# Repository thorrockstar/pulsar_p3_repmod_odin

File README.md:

Open Source Pulsar P3 Replacement Module 'Odin' & 'Loki'
========================================================

This project bundles my source code, binary, schematics and PCB layout files for my own Open Source Pulsar P3 LED watch replacement modules. I do **not** sell those modules or any component and I do **not** do any repairs. This project is purely for the enthusiast, that want to fix a Pulsar LED watch himself or herself, that is far beyond repair otherwise. This project is **not** meant to be used commercially.

The PCB layout is made in a way, allowing it to be opened and edited with the free Eagle version. I prefer the older Eagle 6.6 release, that still was made by CADSoft.

The free trial version of the CAD-Soft Eagle software can be found on CAD-Softs's own FTP server:
http://eagle.autodesk.com/eagle/software-versions/10

P3 Module Types
===============

This project contains two different boards. The **Odin Mark II** board, that can be used, if the **original Litronix** dotty LED display could be rescued. The **Loki** board can be used if the original display is broken and shall be replaced with four USSR made **AL304G replacement** single digit displays with common anodes. See the comments in the schematics.

**Note:** Some of the photos show **older** variants of the boards. So don't get confused. The current Odin Mark II features **4 extra transistors** for driving the common cathodes.

**Important Note:** As the new PCB's have traces and vias/pads on the back side, make sure you put some black isolation tape on top of the plastic carrier *before* placing the new PCB onto it. Otherwise the battery connection wires may short your PCB!

P4 Module Variant
=================

There is a sub-folder called 'p4mod', that contains a module called **Sif**. This one can be used for P4 Executive watches. It has the micro controller on the back side. So, double check the orientation of the chip, when soldering, as the PCB is shown from the top layer in the pictures and you need to turn the PCB over when soldering. Be aware, that you will need to **modify the plastic carrier**. You will be in need to make the open space behind the PCB wider, to be able to place the PCB flush on the P4 plastic carrier. I usually do that by cutting the edges on the top and bottom of the inner opening in order to create a 45 degree angle there.

License Agreement
=================

The software, source code, schematics, drawings and resources are provided to you by the Licensor under the License, as defined below, subject to the following condition.

Without limiting other conditions in the License, the grant of rights under the License will not include, and the License does not grant to you, the right to sell the software, source code, schematics, drawings or resources.

The Licensor does not grant the right to produce watch modules on the base of this work and then sell them as a product for profit.

These schematics, layout and source code files are free software; you can redistribute them and/or modify them under the terms of the GNU General Public License as published by the Free Software Foundation in version 2 of the License.

These source code, schematics, drawings and layout files are distributed in the hope that they will be useful, but WITHOUT ANY WARRANTY; without even the implied warranty of MERCHANTABILITY or FITNESS FOR A PARTICULAR PURPOSE. See the GNU General Public License for more details.

Hardware & Software
===================

This project features a MicroChip PIC18F24J11 MCU. The software can be compiled using Microchip's MPLAB IDE and the XC8 compiler. You can get those free for private use. To flash the controller I used a PICKIT™3 unit. You still get those units second hand or NOS but you can also use a more recent one.

**Module 'Odin' featuring the original display and light sensor.**

(Older Odin 1)

(Newer Odin Mark II)

In the main header file, select the right type of watch module. You find also ready compiled binaries for the 'Odin' and 'Loki' module.

**Module 'Loki' featuring four replacement single digit displays and no light sensor.**

Important
==========
We do **not** do any repairs or deliver any components. This is a pure Open Source project, were I share my files, that I used to create a replacement module for one of my old watches, that was corroded beyond repair. This project shall not be used commercially.

Contributing
============
To contribute to this project you should submit your proposals to the maintainer via GitHub.

Maintainer
==========
Dipl.-Ing.(FH) Roy Schneider

Useful Information
==================

More information about old Pulsar LED watches, can be found here:

Pulsar LED Watch Forum:
http://www.oldpulsars.com/

PCB
===

If you order your PCB at some manufacturer, go for the 1mm material thickness, not more. You need a thin PCB to ensure, you have enough clearance to the watch case glass, when the display has been installed. A traces thickness of 35 µm is good enough. Order the PCB with a solder stop mask. That simplifies soldering a lot. You usually do not need a silk screen. Order ENIG (Electroless Nickel Gold) surface (traces) for best solder results.

Energy Consumption
==================

The watch currently draws about 7 µA (0.007 mA) of current, if the display is not lit up. Assuming your silver oxide batteries would have 160mAh, the battery life time would be a year, depending how often you use the display. You may use Alkaline batteries but I suggest to use Silver Oxide batteries having 1.55V and a larger capacity.

Setting the Time & Date of the Replacement Module
=================================================

To forward the hours, place the magnet in the HOURS recess. To forward the minutes, place the magnet in the MINUTES recess. Keep in mind that the watch will stop counting the time, if you have forwarded the minutes, until you will press the first time the readout TIME button. This gives you an easy way to set the watch second-accurate, by setting the watch one minute into the future and then wait until the reference clock wraps to that very minute. If you press the TIME button in that moment, the watch will continue counting the time, having set the seconds to zero. To forward the month hold the DATE button pressed and place the magnet in the HOUR recess. To forward the day hold the DATE and TIME buttons pressed at the same time and place the magnet in the HOUR recess. This replacement module adds the weekday, the year and the light sensor read-out to the watch. Refer to the next chapter for setting them.

Settings the Extra Features of the Firmware not included in the original P3
===========================================================================

The firmware for this replacement module adds two additional functions to the watch. It adds the weekday and the year. To set the year hold the DATE and TIME button pressed and forward the year by putting the magnet into the MIN recess. To set the weekday hold only the DATE button pressed and forward the weekday by putting the magnet into the MIN recess. If you face the issue that you set the year instead of the weekday, then the magnet is very strong and engages not only the MIN but also the TIME reed contact. Try turning the magnet around in that case.

Optional Alarm Feature of the 'Loki Module'
============================================

This feature is only available for the 'Loki' modules, using the USSR made replacement displays. You can use the output RC2 of the micro controller in order to drive a disc piezo buzzer with a 820Ohm...1kOhm resistor in series. To use that feature turn the ALARM option on in the main.h header file and rebuild the binary.

**Note:**

Don't expect the alarm to be loud... it will not be loud enough to wake you up, simply because it is silenced by the massive metal case of the watch. :-)

**Set Alarm**

In order to set the alarm, press the TIME (hold) and then the DATE (hold) button in this exact order ands keep them pressed together. Now you can place the magnet in the HOUR or MIN recess to set the alarm.

**Toggle Alarm (on/off)**

To turn the alarm on or off press the TIME (hold) and then the DATE (hold) button in this exact order, then release the DATE button and press DATE again, while holding TIME still pressed, in order to toggle the alarm. A little dot on the right of the last AL304G display will indicate if the alarm is on or off.

Light Sensor Readout
====================

This applies only to the 'Odin' modules, if the light sensor option has been turned on. If you hold the DATE button pressed for more than a second, the watch will show the weekday and then, if you still keep the button pressed, the year. If you keep the button even longer pressed, a number will appear, that reflects the light sensor value. On normal daylight, that value shall be between two and four. On strong sun light five to six. If you are in dim light, the watch shall show one or zero. This readout is meant to make it easy to check, if the light sensor is working correctly.

Calibration
===========

The real-time crystal signal can be calibrated, so that the watch can provide an error of less than three seconds per month. If using the vintage original crystal, you will have easily 5 to 20 seconds drift per week, as those crystals are often hopelessly out tuned. By pressing the DATE button and holding it pressed, until the year or light sensor read out appears and then pressing the TIME button as well for a second, you will enter the drift calibration mode. You can now release the TIME button but keep the DATE pressed and use the magnet in the MIN recess to increase the calibration value. Use the HOUR recess to decrease the calibration value again. A positive value will speed up the watch by x\*0.6 seconds per week. A negative value will slow down the watch by x\*0.6 seconds by week. You can adjust the watch by a maximum ±38.76 seconds per week.

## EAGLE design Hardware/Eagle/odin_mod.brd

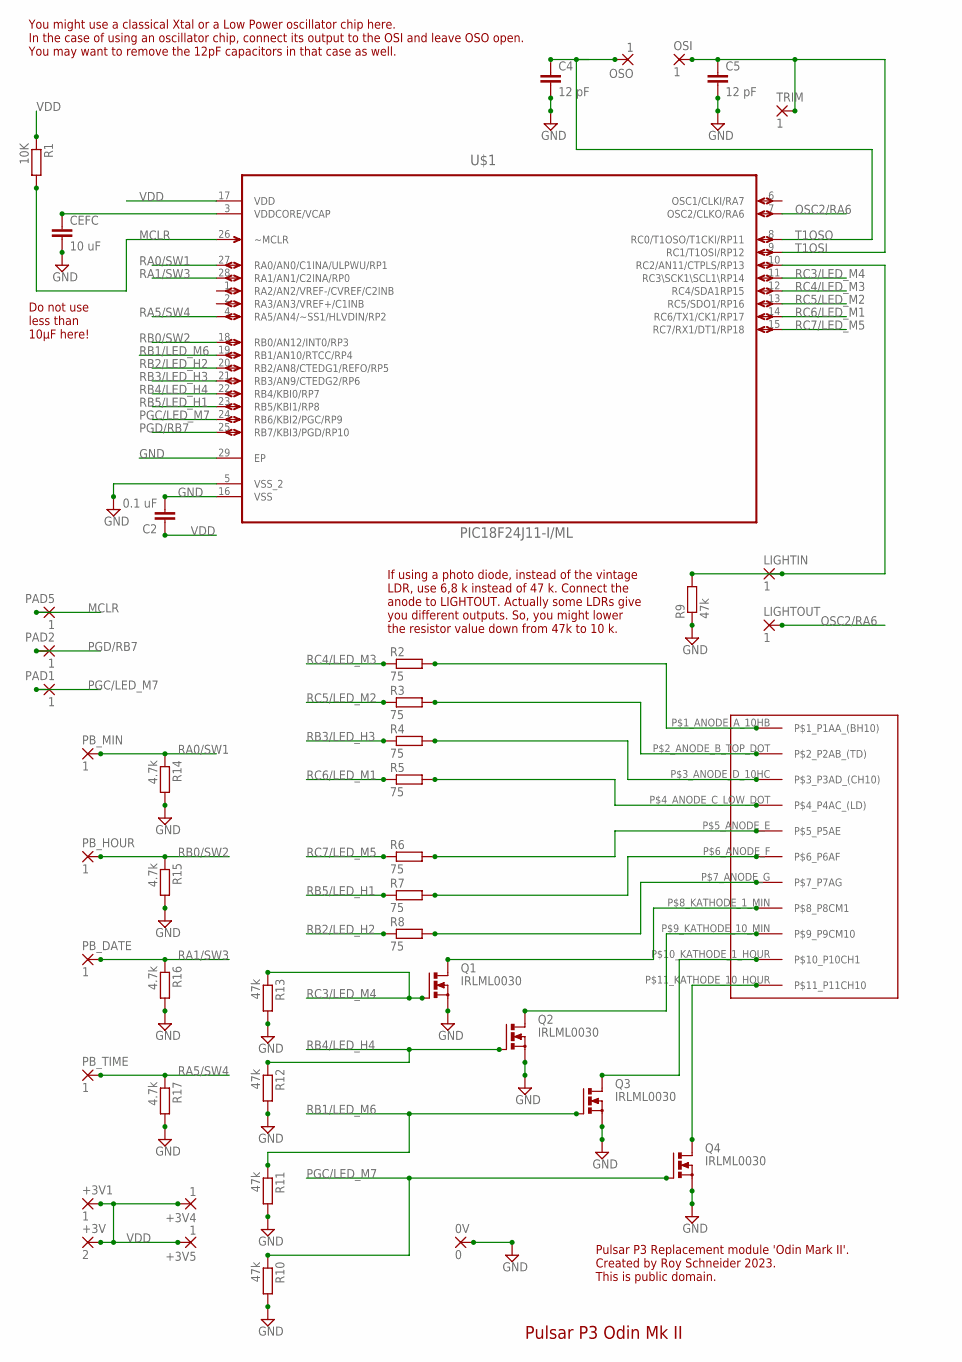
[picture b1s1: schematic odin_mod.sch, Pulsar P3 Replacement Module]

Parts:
0V: 0; SMD1,27-2,54
+3V: 2; SMD1,27-2,54
+3V1, +3V4, +3V5: 1; SMD1,27-2,54
C2: 0.1 uF; C0603
C4, C5: 12 pF; C0603
CEFC: 10 uF; C0603
LIGHTIN: 1; SMD1,27-2,54
LIGHTOUT: 1; SMD1,27-2,54
OSI: 1; SMD1,27-2,54
OSO: 1; SMD1,27-2,54
PAD1, PAD2, PAD5: 1; SMD1,27-2,54
PB_DATE: 1; SMD1,27-2,54
PB_HOUR: 1; SMD1,27-2,54
PB_MIN: 1; SMD1,27-2,54
PB_TIME: 1; SMD1,27-2,54
Q1, Q2, Q3, Q4: IRLML0030; SOT-23
R1: 10K; R0402
R2, R3, R4, R5, R6, R7, R8: 75; R0402
R9, R10, R11, R12, R13: 47k; R0402
R14, R15, R16, R17: 4.7k; R0402
TRIM: 1; SMD1,27-2,54
U$1: PIC18F24J11-I/ML; QFN65P600X600X100-29N
U$3: PULSAR_P3_DISPLAY; PULSAR_P3_LED_DISPLAY

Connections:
GND: 0V.1, C2.2, C4.2, C5.2, CEFC.2, Q1.P2 (S), Q2.P2 (S), Q3.P2 (S), Q4.P2 (S), R9.1, R10.2, R11.2, R12.2, R13.2, R14.2, R15.2, R16.2, R17.2, U$1.5 (VSS_2), U$1.16 (VSS), U$1.29 (EP)
MCLR: PAD5.1, R1.2, U$1.26 (~MCLR)
unnamed: LIGHTIN.1, R9.2, U$1.10 (RC2/AN11/CTPLS/RP13)
unnamed: R2.2, U$3.P$1_ANODE_A_10HB (P$1_P1AA_(BH10))
unnamed: R3.2, U$3.P$2_ANODE_B_TOP_DOT (P$2_P2AB_(TD))
unnamed: R4.2, U$3.P$3_ANODE_D_10HC (P$3_P3AD_(CH10))
unnamed: R5.2, U$3.P$4_ANODE_C_LOW_DOT (P$4_P4AC_(LD))
unnamed: R6.2, U$3.P$5_ANODE_E (P$5_P5AE)
unnamed: R7.2, U$3.P$6_ANODE_F (P$6_P6AF)
unnamed: R8.2, U$3.P$7_ANODE_G (P$7_P7AG)
unnamed: Q4.P3 (D), U$3.P$11_KATHODE_10_HOUR (P$11_P11CH10)
unnamed: Q3.P3 (D), U$3.P$10_KATHODE_1_HOUR (P$10_P10CH1)
unnamed: Q2.P3 (D), U$3.P$9_KATHODE_10_MIN (P$9_P9CM10)
unnamed: Q1.P3 (D), U$3.P$8_KATHODE_1_MIN (P$8_P8CM1)
OSC2/RA6: LIGHTOUT.1, U$1.7 (OSC2/CLKO/RA6)
PGC/LED_M7: PAD1.1, Q4.P1 (G), R10.1, U$1.24 (RB6/KBI2/PGC/RP9)
PGD/RB7: PAD2.1, U$1.25 (RB7/KBI3/PGD/RP10)
RA0/SW1: PB_MIN.1, R14.1, U$1.27 (RA0/AN0/C1INA/ULPWU/RP1)
RA1/SW3: PB_DATE.1, R16.1, U$1.28 (RA1/AN1/C2INA/RP0)
RA5/SW4: PB_TIME.1, R17.1, U$1.4 (RA5/AN4/~SS1/HLVDIN/RP2)
RB0/SW2: PB_HOUR.1, R15.1, U$1.18 (RB0/AN12/INT0/RP3)
RB1/LED_M6: Q3.P1 (G), R11.1, U$1.19 (RB1/AN10/RTCC/RP4)
RB2/LED_H2: R8.1, U$1.20 (RB2/AN8/CTEDG1/REFO/RP5)
RB3/LED_H3: R4.1, U$1.21 (RB3/AN9/CTEDG2/RP6)
RB4/LED_H4: Q2.P1 (G), R12.1, U$1.22 (RB4/KBI0/RP7)
RB5/LED_H1: R7.1, U$1.23 (RB5/KBI1/RP8)
RC3/LED_M4: Q1.P1 (G), R13.1, U$1.11 (RC3\SCK1\SCL1\RP14)
RC4/LED_M3: R2.1, U$1.12 (RC4/SDA1RP15)
RC5/LED_M2: R3.1, U$1.13 (RC5/SDO1/RP16)
RC6/LED_M1: R5.1, U$1.14 (RC6/TX1/CK1/RP17)
RC7/LED_M5: R6.1, U$1.15 (RC7/RX1/DT1/RP18)
T1OSI: C5.1, OSI.1, TRIM.1, U$1.9 (RC1/T1OSI/RP12)
T1OSO: C4.1, OSO.1, U$1.8 (RC0/T1OSO/T1CKI/RP11)
VDD: +3V.1, +3V1.1, +3V4.1, +3V5.1, C2.1, R1.1, U$1.17 (VDD)
VDDCORE/VCAP: CEFC.1, U$1.3 (VDDCORE/VCAP)

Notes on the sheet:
You might use a classical Xtal or a Low Power oscillator chip here. In the case of using an oscillator chip, connect its output to the OSI and leave OSO open. You may want to remove the 12pF capacitors in that case as well.
Pulsar P3 Replacement module 'Odin Mark II'. Created by Roy Schneider 2023. This is public domain.
Pulsar P3 Odin Mk II
If using a photo diode, instead of the vintage LDR, use 6,8 k instead of 47 k. Connect the anode to LIGHTOUT. Actually some LDRs give you different outputs. So, you might lower the resistor value down from 47k to 10 k.
Do not use less than 10µF here!

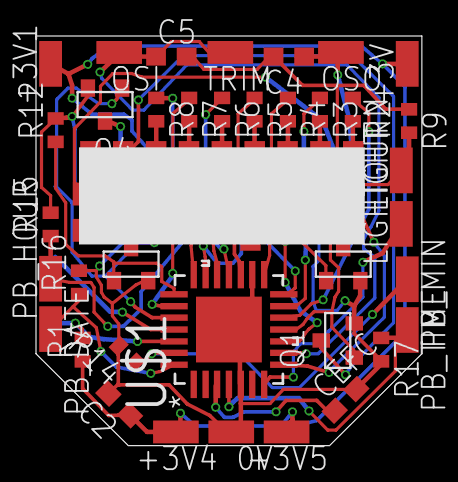
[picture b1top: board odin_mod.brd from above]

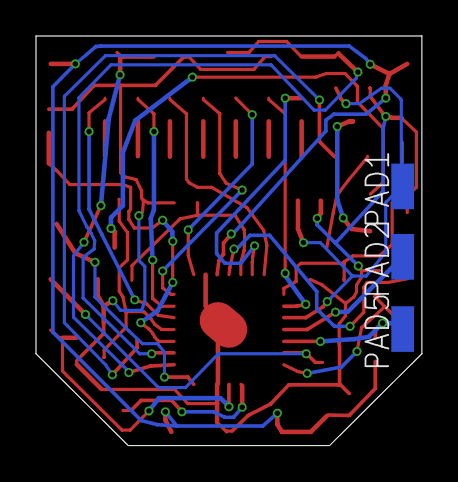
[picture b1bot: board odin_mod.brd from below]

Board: 2 copper layers, 21.4 x 22.8 mm, 44 parts (3 on the bottom side), 35 nets.

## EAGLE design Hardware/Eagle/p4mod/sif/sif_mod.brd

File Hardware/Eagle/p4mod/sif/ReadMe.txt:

Hi!

This module can be used for P4 Executive watches. It has the micro controller on the back side.
So, double check the orientation of the chip as the PCB is shown from the top layer in the pictures but you have to flip around the PCB, when soldering the chip.

Be aware, that you will need to **modify the plastic carrier** for the **P4 version**.
You will be in need to make the open space wider to be able to place the PCB flush on the P4 plastic carrier. I usually do that by cutting the edges on the upper and lower side of the inner open space and create a 45 degree angle there. See the pictures.

In the header file of the main.h do not forget to set...

#define APP_WATCH_TYPE_BUILD    APP_PULSAR_P4_WRIST_WATCH_12H_SIF_MARK_II_MOD

...when building for the P4 SiF module! You can also use the pre-compiled binary called "pulsar_p4_sif_litronix_firmware.hex" for flashing the micro controller instead.

Kind regards

Roy

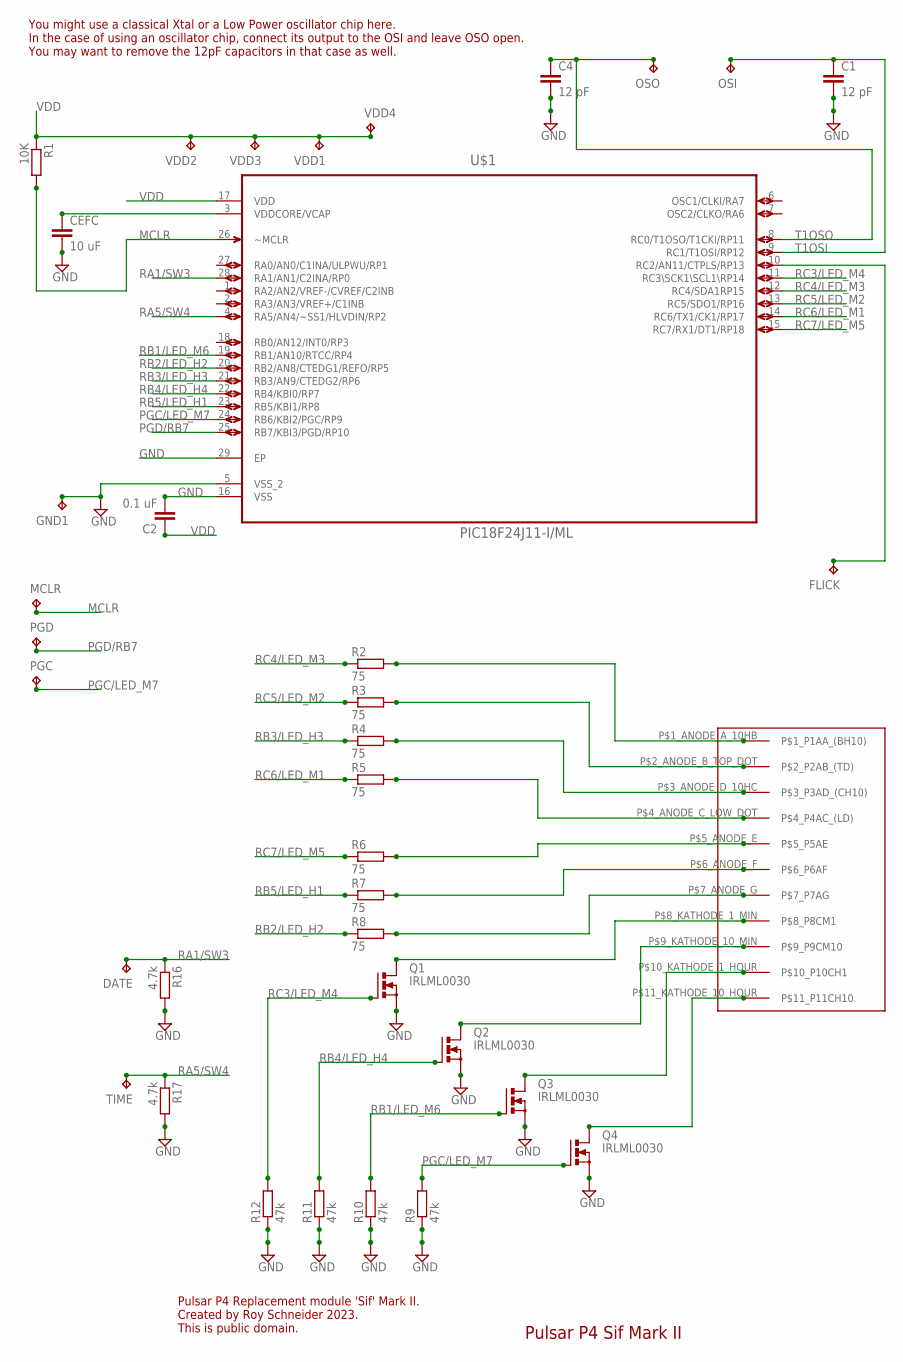
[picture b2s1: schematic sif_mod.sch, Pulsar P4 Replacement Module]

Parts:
C1, C4: 12 pF; C0402K
C2: 0.1 uF; C0402K
CEFC: 10 uF; C0603
DATE: TPTP08SQ; TP08SQ
FLICK: TPTP08SQ; TP08SQ
GND1: TPTP08SQ; TP08SQ
MCLR: TPTP06SQ; TP06SQ
OSI: TPTP08SQ; TP08SQ
OSO: TPTP08SQ; TP08SQ
PGC: TPTP06SQ; TP06SQ
PGD: TPTP06SQ; TP06SQ
Q1, Q2, Q3, Q4: IRLML0030; SOT-23
R1: 10K; R0402
R2, R3, R4, R5, R6, R7, R8: 75; R0402
R9, R10, R11, R12: 47k; R0402
R16, R17: 4.7k; R0402
TIME: TPTP08SQ; TP08SQ
U$1: PIC18F24J11-I/ML; QFN65P600X600X100-29N
U$2: PULSAR_P4_DISPLAYPULSAR_P4_LED_DISPLAY; PULSAR_P3_LED_DISPLAY
VDD1, VDD2, VDD3, VDD4: TPTP08SQ; TP08SQ

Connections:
GND: C1.2, C2.2, C4.2, CEFC.2, GND1.TP, Q1.P2 (S), Q2.P2 (S), Q3.P2 (S), Q4.P2 (S), R9.1, R10.1, R11.1, R12.1, R16.2, R17.2, U$1.5 (VSS_2), U$1.16 (VSS), U$1.29 (EP)
MCLR: MCLR.TP, R1.2, U$1.26 (~MCLR)
unnamed: FLICK.TP, U$1.10 (RC2/AN11/CTPLS/RP13)
unnamed: R8.2, U$2.P$7_ANODE_G (P$7_P7AG)
unnamed: R7.2, U$2.P$6_ANODE_F (P$6_P6AF)
unnamed: R6.2, U$2.P$5_ANODE_E (P$5_P5AE)
unnamed: R5.2, U$2.P$4_ANODE_C_LOW_DOT (P$4_P4AC_(LD))
unnamed: R4.2, U$2.P$3_ANODE_D_10HC (P$3_P3AD_(CH10))
unnamed: R3.2, U$2.P$2_ANODE_B_TOP_DOT (P$2_P2AB_(TD))
unnamed: R2.2, U$2.P$1_ANODE_A_10HB (P$1_P1AA_(BH10))
unnamed: Q2.P3 (D), U$2.P$9_KATHODE_10_MIN (P$9_P9CM10)
unnamed: Q3.P3 (D), U$2.P$10_KATHODE_1_HOUR (P$10_P10CH1)
unnamed: Q4.P3 (D), U$2.P$11_KATHODE_10_HOUR (P$11_P11CH10)
unnamed: Q1.P3 (D), U$2.P$8_KATHODE_1_MIN (P$8_P8CM1)
PGC/LED_M7: PGC.TP, Q4.P1 (G), R9.2, U$1.24 (RB6/KBI2/PGC/RP9)
PGD/RB7: PGD.TP, U$1.25 (RB7/KBI3/PGD/RP10)
RA1/SW3: DATE.TP, R16.1, U$1.28 (RA1/AN1/C2INA/RP0)
RA5/SW4: R17.1, TIME.TP, U$1.4 (RA5/AN4/~SS1/HLVDIN/RP2)
RB1/LED_M6: Q3.P1 (G), R10.2, U$1.19 (RB1/AN10/RTCC/RP4)
RB2/LED_H2: R8.1, U$1.20 (RB2/AN8/CTEDG1/REFO/RP5)
RB3/LED_H3: R4.1, U$1.21 (RB3/AN9/CTEDG2/RP6)
RB4/LED_H4: Q2.P1 (G), R11.2, U$1.22 (RB4/KBI0/RP7)
RB5/LED_H1: R7.1, U$1.23 (RB5/KBI1/RP8)
RC3/LED_M4: Q1.P1 (G), R12.2, U$1.11 (RC3\SCK1\SCL1\RP14)
RC4/LED_M3: R2.1, U$1.12 (RC4/SDA1RP15)
RC5/LED_M2: R3.1, U$1.13 (RC5/SDO1/RP16)
RC6/LED_M1: R5.1, U$1.14 (RC6/TX1/CK1/RP17)
RC7/LED_M5: R6.1, U$1.15 (RC7/RX1/DT1/RP18)
T1OSI: C1.1, OSI.TP, U$1.9 (RC1/T1OSI/RP12)
T1OSO: C4.1, OSO.TP, U$1.8 (RC0/T1OSO/T1CKI/RP11)
VDD: C2.1, R1.1, U$1.17 (VDD), VDD1.TP, VDD2.TP, VDD3.TP, VDD4.TP
VDDCORE/VCAP: CEFC.1, U$1.3 (VDDCORE/VCAP)

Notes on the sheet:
You might use a classical Xtal or a Low Power oscillator chip here. In the case of using an oscillator chip, connect its output to the OSI and leave OSO open. You may want to remove the 12pF capacitors in that case as well.
Pulsar P4 Replacement module 'Sif' Mark II. Created by Roy Schneider 2023. This is public domain.
Pulsar P4 Sif Mark II

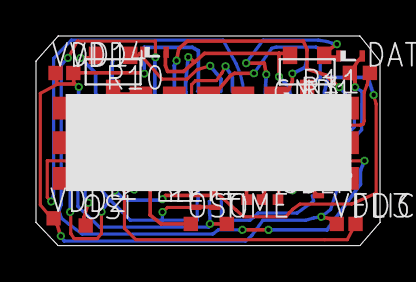
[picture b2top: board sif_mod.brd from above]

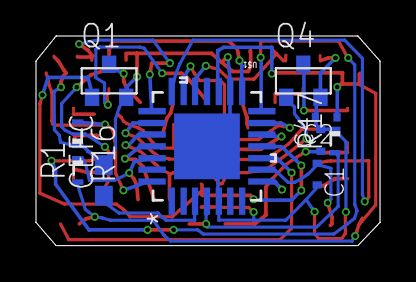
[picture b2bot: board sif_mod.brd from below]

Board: 2 copper layers, 19.1 x 11.6 mm, 37 parts (10 on the bottom side), 32 nets.

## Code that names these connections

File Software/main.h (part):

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/**
 * Define all the possible watch types, supported by this WatchApp.
 * 
 * Maximum output current by PORTB, PORTC and RA6 I/O pin is 25 mA.
 */

// P3 - Original Litronix P2/P3 display.
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
    // TIME
    #define PB0_PORT_BITS   PORTAbits
    #define PB0_PIN         RA5
    // DATE
    #define PB1_PORT_BITS   PORTAbits
    #define PB1_PIN         RA1
    // HOUR
    #define PB2_PORT_BITS   PORTBbits
    #define PB2_PIN         RB0
    // MIN
    #define PB3_PORT_BITS   PORTAbits
    #define PB3_PIN         RA0

#elif (APP_WATCH_TYPE_BUILD==APP_PULSAR_WRIST_WATCH_12H_LEGACY_MOD)

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
    // TIME
    #define PB0_PORT_BITS   PORTAbits
    #define PB0_PIN         RA5
    // DATE
    #define PB1_PORT_BITS   PORTAbits
    #define PB1_PIN         RA1
    // HOUR
    #define PB2_PORT_BITS   PORTBbits
    #define PB2_PIN         RB0
    // MIN
    #define PB3_PORT_BITS   PORTAbits
    #define PB3_PIN         RA0

#elif (APP_WATCH_TYPE_BUILD==APP_PULSAR_P3_WRIST_WATCH_24H_LOKI_MOD)

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
    // TIME
    #define PB0_PORT_BITS   PORTAbits
    #define PB0_PIN         RA5
    // DATE
    #define PB1_PORT_BITS   PORTAbits
    #define PB1_PIN         RA1
    // HOUR
    #define PB2_PORT_BITS   PORTBbits
    #define PB2_PIN         RB0
    // MIN
    #define PB3_PORT_BITS   PORTAbits
    #define PB3_PIN         RA0

#elif (APP_WATCH_TYPE_BUILD==APP_PULSAR_P4_WRIST_WATCH_24H_HEL_MOD)

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
    // TIME
    #define PB0_PORT_BITS   PORTAbits
    #define PB0_PIN         RA5
    // DATE
    #define PB1_PORT_BITS   PORTAbits
    #define PB1_PIN         RA1
    // HOUR
    #define PB2_PORT_BITS   PORTBbits
    #define PB2_PIN         RB0
    // MIN
    #define PB3_PORT_BITS   PORTAbits
    #define PB3_PIN         RA0
    // WRIST
    #define PB4_PORT_BITS   PORTCbits
    #define PB4_PIN         RC2

#elif (APP_WATCH_TYPE_BUILD==APP_PULSAR_WRIST_WATCH_12H_SIF_LEGACY_MOD)

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
    // TIME
    #define PB0_PORT_BITS   PORTAbits
    #define PB0_PIN         RA5
    // DATE
    #define PB1_PORT_BITS   PORTAbits
    #define PB1_PIN         RA1
    // HOUR
    #define PB2_PORT_BITS   PORTBbits
    #define PB2_PIN         RB0
    // MIN
    #define PB3_PORT_BITS   PORTAbits
    #define PB3_PIN         RA0
    // WRIST
    #define PB4_PORT_BITS   PORTCbits
    #define PB4_PIN         RC2

#elif (APP_WATCH_TYPE_BUILD==APP_PULSAR_P4_WRIST_WATCH_12H_SIF_MARK_II_MOD)

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
    // TIME
    #define PB0_PORT_BITS   PORTAbits
    #define PB0_PIN         RA5
    // DATE
    #define PB1_PORT_BITS   PORTAbits
    #define PB1_PIN         RA1
    // HOUR
    #define PB2_PORT_BITS   PORTBbits
    #define PB2_PIN         RB0
    // MIN
    #define PB3_PORT_BITS   PORTAbits
    #define PB3_PIN         RA0
    // WRIST
    #define PB4_PORT_BITS   PORTCbits
    #define PB4_PIN         RC2

#elif APP_WATCH_TYPE_BUILD==APP_PROTOTYPE_BREAD_BOARD

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
    // TIME
    #define PB0_PORT_BITS   PORTAbits
    #define PB0_PIN         RA0
    // DATE
    #define PB1_PORT_BITS   PORTBbits
    #define PB1_PIN         RB0
    // HOUR
    #define PB2_PORT_BITS   PORTAbits
    #define PB2_PIN         RA1
    // MIN
    #define PB3_PORT_BITS   PORTAbits
    #define PB3_PIN         RA2
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* Display port definitions */

// Anodes/Segments
#define LED_AA_B        PORTCbits.RC4
#define LED_AA_B_MASK   16

#define LED_AB_TD       PORTCbits.RC5
#define LED_AB_TD_MASK  32

#define LED_AC_LD       PORTCbits.RC6
#define LED_AC_LD_MASK  64

#define LED_AD_C        PORTBbits.RB3
#define LED_AD_C_MASK   8

#define LED_AE          PORTCbits.RC7
#define LED_AE_MASK     128

#define LED_AF          PORTBbits.RB5
#define LED_AF_MASK     32

#define LED_AG          PORTBbits.RB2
#define LED_AG_MASK     4

// Cathods/Multiplexing
#define LED_1M          PORTCbits.RC3
#define LED_10M         PORTBbits.RB4
#define LED_1H          PORTBbits.RB1
#define LED_10H         PORTBbits.RB6

// Light sensor power
#define PWR_LGTH_SENSOR PORTAbits.RA6

// Optional date dot for the 24h Loki/Hel mods. Conflicts with the light sensor.
#define LED_DATE_DOT    PORTAbits.RA6

/* Debounce and hold times for the buttons. */

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
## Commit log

2020-11-12 Added layout and source files.
2020-11-12 Added layer images.
2020-11-12 Improved Readme file.
2020-11-12 Added PCB preview files.
2020-11-14 Added loki board using l104g replacement displays.
2020-11-15 Added support for 24h module Loki, featuring a different display.
2020-11-15 Update the watch application to support the Loki module.
2020-11-15 Updated Loki board file.
2020-11-15 Fixed cathodes handling for USSR made replacement display.
2020-11-19 Added resitor for date dot, if using the USSR replacement made display.
2020-11-21 Merged.
2020-11-22 Added toggling between common anode/cathode for Loki boards.
2020-11-28 Increased TRACE and VIA width were possible.
2020-11-30 Added frame for alarm buzzer feature.
2020-12-01 Added alarm decimal point.
2020-12-01 Added buzzer PWM output feature.
2020-12-01 Reviewed buzzer code.
2020-12-02 Worked further on the buzzer alarm feature.
2020-12-07 Reworked 24h model.
2020-12-07 If no light sensor is used, turn all IO to digital.
2020-12-07 Improved layout of Loki board using USSR made replacement display.
2020-12-10 Fixed changing display state while multiplexing.
2020-12-12 Improved setting year.
2020-12-13 Added PDF's of schematics and board files.
2020-12-13 Got alarm working.
2020-12-15 Updated source code.
2020-12-19 Optimized layout for manual soldering.
2020-12-19 Cleaned up code and comments.
2020-12-20 Updated description.
2020-12-20 Added module image.
2020-12-20 Updated project description.
2020-12-20 Added the buzzer solder pad for the 'Loki' board.
2020-12-22 Connected unused dots for digit 1 and 3.
2020-12-22 Small layout improvements.
2020-12-30 After feedback from the manufacturer of the PCB the outer PCB shape has been improved.
2021-01-08 Fixed some DRC issues.
2021-01-10 Added resitor for piezo.
2021-01-10 Added variant for common anode displays, type AL304G.
2021-01-10 Fixed alarm dot and 24h default setup of the hours.
2021-01-21 Added startup beep.
2021-01-21 Improved macro names.
2021-01-24 Updated resitor values and fine tuned some traces.
2021-01-24 Added close-up of a hand soldered loki module.
2021-02-13 Added RTC calibration feature.
2021-02-18 Optimized layout and Litronix display footprint.
2021-02-26 Moved GND-VIA to make it unlikely to short it, when soldering the resistor next to it.
2021-02-26 Update ODIN Firmware.
2021-02-27 Fixed resistor value.
2021-03-07 Added lowering the calibarion value via the HOUR notch.
2021-03-13 Added detail pictures.
2021-03-14 Updated pdf files.
2021-03-14 Reviewed.
2021-03-15 Adjusted trace width.
2021-05-05 Reworked layout for odin and loki boards.
2021-05-10 Started to add support for the P4 (403) replacement modules.
2021-05-13 Fine tuned light sensor impact on display brightness.
2021-05-13 Firmware update, traces optimized.
2021-05-15 Lowered impact of light sensor.
2021-05-15 Updated firmware.
2021-07-25 Added comments, reviewed code.
2021-08-24 Updated information about the project.
2021-08-25 Optimized Odin and Loki layout.
2021-08-26 Updated instructions about adjusting the drift calibration.
2021-08-30 Improved plausibility test for RTC day of month.
2021-09-05 Optimized the traces.
2021-09-05 Update project information.
2021-09-17 Updated instructions.
2021-11-27 Reviewed boards and code.
2021-12-30 Updated pictures.
2022-01-02 Granted longer display lit up time on a wrist flick event.
2022-01-04 Added new photo.
2022-01-09 Power consumption for ODIN module is now down to 7uA.
2022-01-09 Updated info text.
2022-01-12 Updated default year to 2022.
2022-01-22 Updated PCB previews.
2022-08-16 Reviewed Odin module.
2022-10-23 Updated schematics comments.
2022-10-23 Added P4 Executive Module featuring the original Litronix made display.
2022-10-23 Updated firmware binary.
2022-10-23 Cleaned up header file.
2022-10-24 Updated project ReadMe.
2022-10-24 Added S4 Sif ReadMe.
2022-11-12 If wrist flick and button is indicated more or less together, the button will restart the lit-up-counter.
2022-11-12 Updated Sif firmware binary.
2022-12-17 Pushed VCAP to the bootm layer.
2023-01-07 Optimizations.
2023-01-07 Updated P3 Odin binary.
2023-01-07 Added example pictures.
2023-01-08 Optimized C code after having reviewed the assembly listing.
2023-01-14 Updated P4 module Sif files.
2023-01-15 Updated default year to 2023.
2023-02-11 Updated P3 Loki firmware binaries.
2023-02-15 Optimized SiF layout.
2023-08-25 Improved one trace to make it less likely to short it when soldering the board.
2023-08-27 Updated P4 Sif documents and images.
2023-11-06 Added support for Odin Mark II using nmos transistors for the common cathodes.
2023-11-11 Released ODIN MkII featuring n-mos transistors for the common cathodes.
2023-11-11 Updated image files.
2023-11-11 Added programmer kpinout.
2023-11-11 Updated images.
2023-11-11 Updated Read Me file.
2023-11-11 Added loki pcb preview.
2023-11-11 Added odin mk II pcb preview.
2023-11-19 Reworked PCB edges for the Sif module.
2023-11-21 Made Sif board edges wider.
2023-12-05 Lowered values of the segment resistors for the Sif board.
2023-12-06 Added odin mark ii image with the display populated.
2023-12-06 Added odin mk ii wiring.
2023-12-06 Updated wiring drawing.
2023-12-18 Added note about taping the plastic carrier.
2023-12-23 Upgraded Sif module to use nmos transistors for the common cathodes.
2023-12-23 Added required software changes for the upgraded SiF module.
2023-12-23 Updated footprint of 10 uF ceramic cap to 0602.
2023-12-25 Updated Readme and images.
2024-01-03 Having set the default year to 2024.
2024-01-03 Moved Frist Flick pads.
2024-01-04 Added ODIN parts list.
2024-01-04 Added Sif part list.
2024-01-04 Added Loki part list.
2024-01-05 Lowered resistor values a bit.
2024-01-05 Updated Loki software to feature 2024 as default year.
2024-01-06 Eliminated one display pin pass-through.
2024-01-14 Added more support for a table clock.
2024-01-15 Code reviewed.
2024-01-15 Removed Nixi support and branched it out.
2024-01-20 Tested ONE-BUTTON mode.
2024-05-12 Improved segment resistor values.
2024-05-12 Lowered segment resistors and optimized traces.
2024-10-25 Optimized ODIN II layout by means of having more space to solder the two transistors below the display.
2024-10-27 Increased trace with of some connections.
2025-04-26 Set default year to 2025.
2025-05-04 Removed VFD table clock project from the wrist watch source code.
2025-08-16 Added overall DATE/TIME button timeout.

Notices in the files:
Software/main.h:
Copyright (c) 2020-25 Roy Schneider
modify it under the terms of the GNU General Public License
work to be covered by the GNU General Public License. However
accordance with section (3) of the GNU General Public License.
